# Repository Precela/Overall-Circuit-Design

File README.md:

# Overall-Circuit-Design
Schematic and PCB design for AR101

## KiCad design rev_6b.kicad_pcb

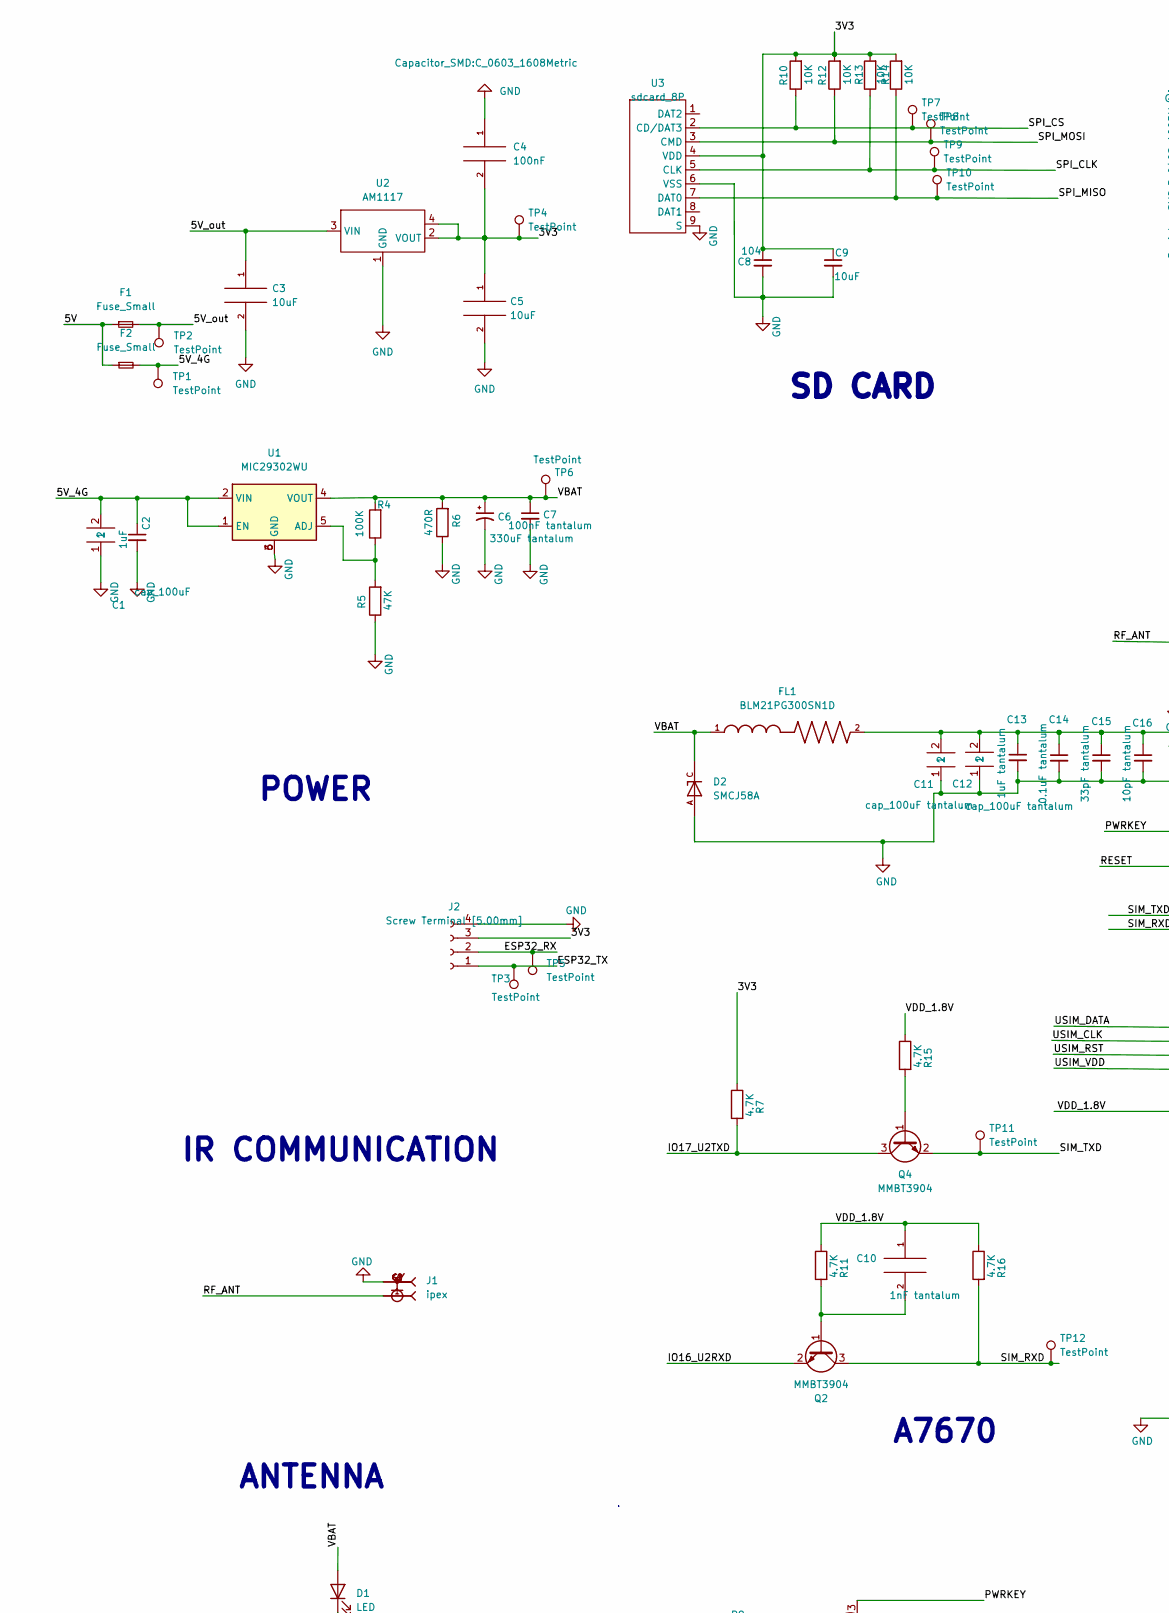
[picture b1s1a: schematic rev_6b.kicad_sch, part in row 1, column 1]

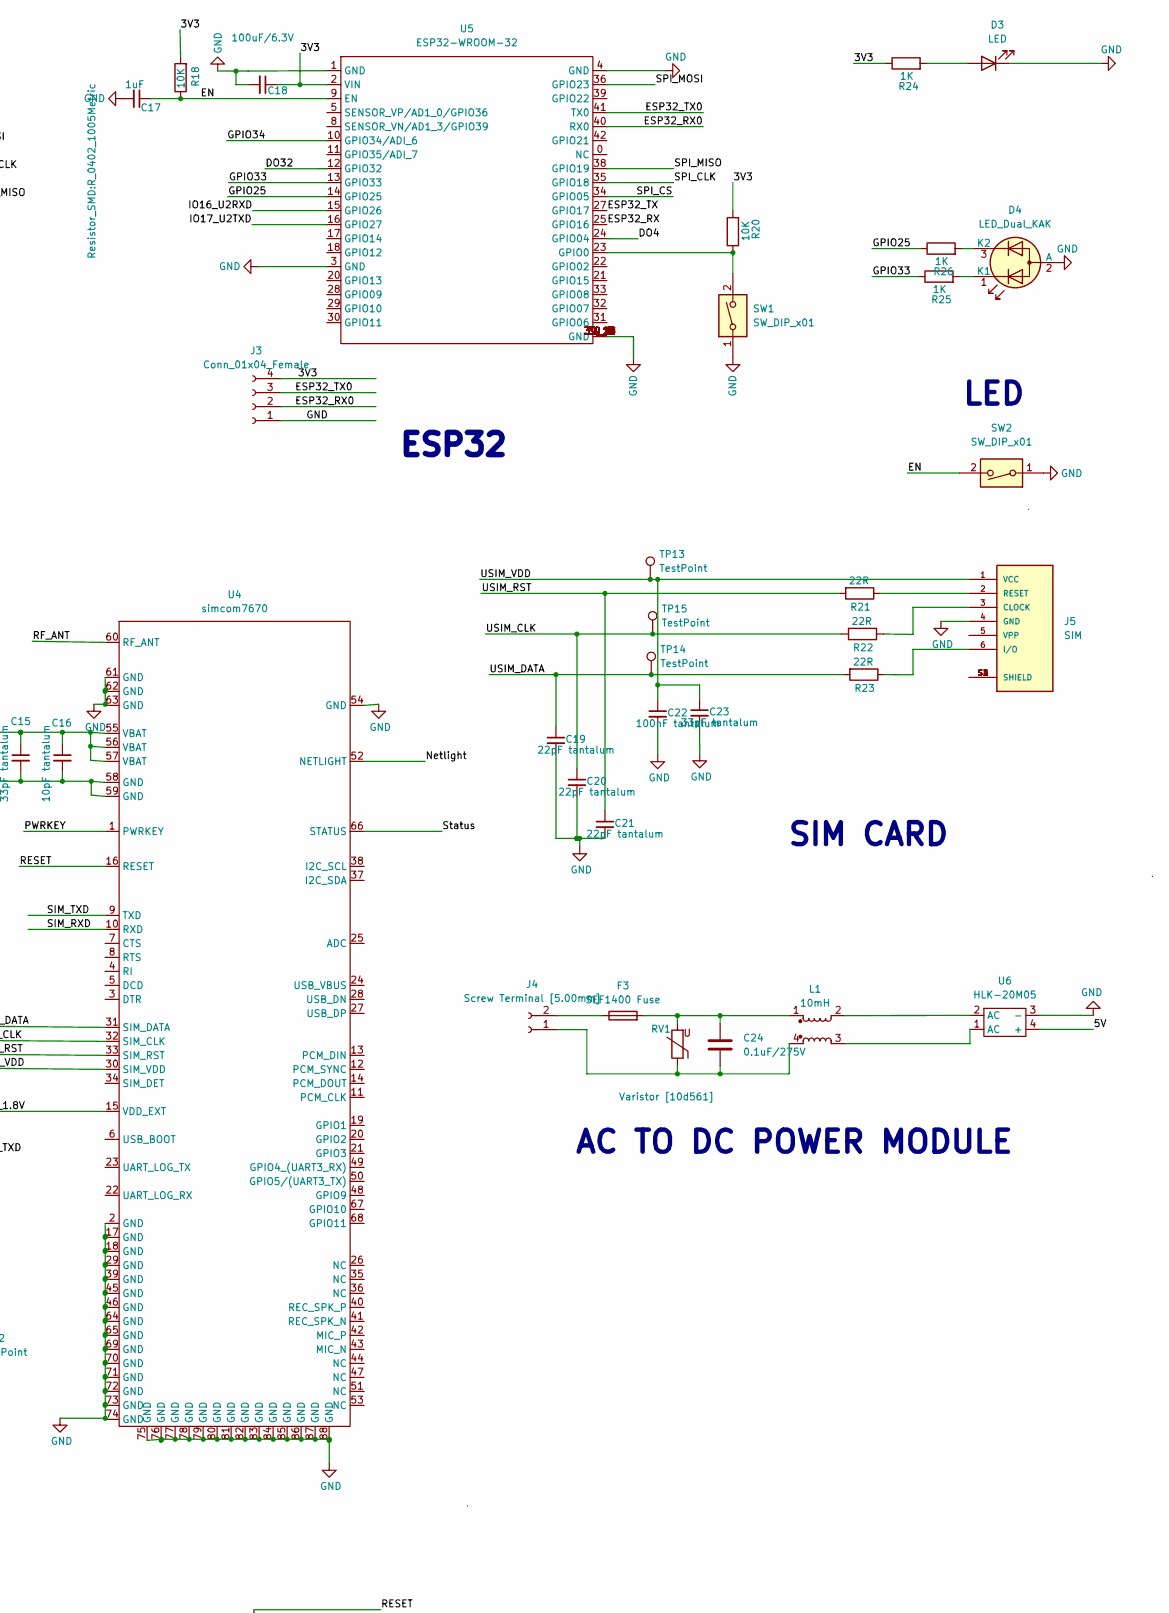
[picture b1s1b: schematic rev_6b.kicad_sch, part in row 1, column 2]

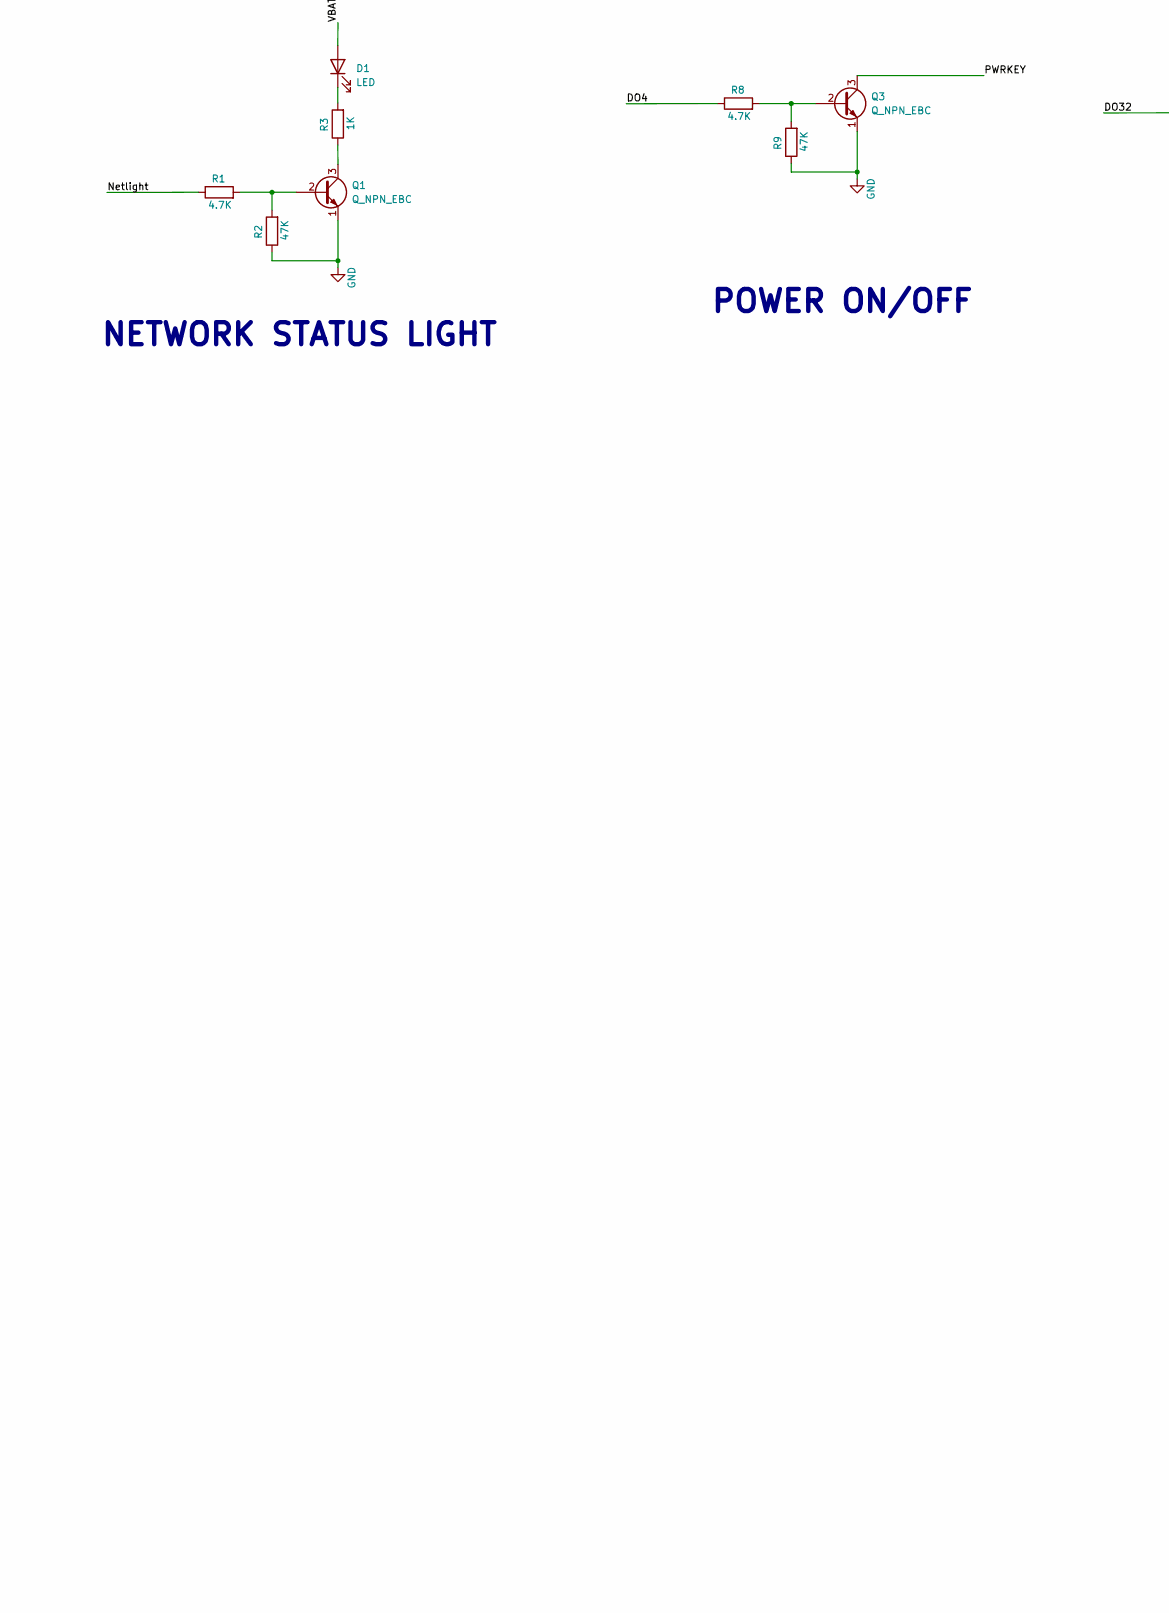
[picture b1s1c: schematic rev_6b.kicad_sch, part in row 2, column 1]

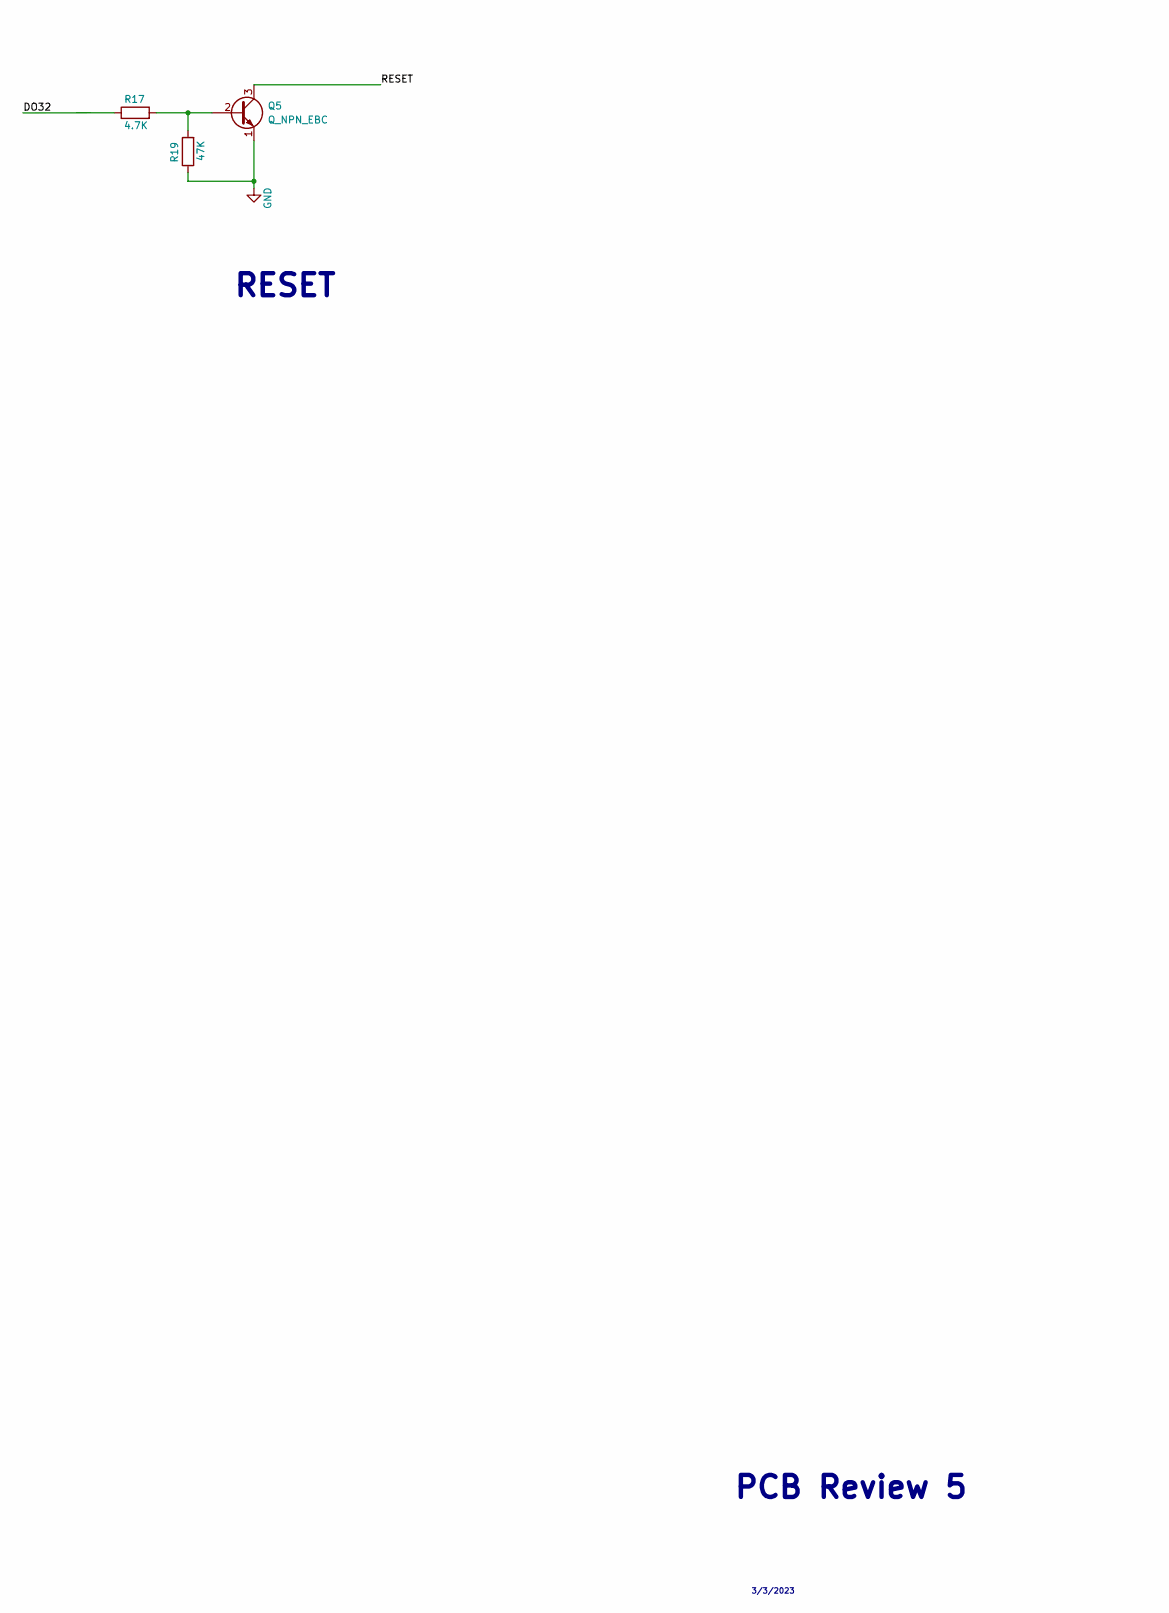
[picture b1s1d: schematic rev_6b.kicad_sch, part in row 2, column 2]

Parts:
C1: cap_100uF; C_0603_1608Metric
C2, C17: 1uF; C_0603_1608Metric
C3, C5, C9: 10uF; C_0603_1608Metric
C4: 100nF; C_0603_1608Metric
C6: 330uF tantalum; CAPMP7343X310N
C7, C22: 100nF tantalum; C_0603_1608Metric
C8: 104; C_0603_1608Metric
C10: 1nF tantalum; C_0603_1608Metric_Pad1.08x0.95mm_HandSolder
C11, C12: cap_100uF tantalum; C_0805_2012Metric
C13: 1uF tantalum; C_0603_1608Metric
C14: 0.1uF tantalum; C_1206_3216Metric
C15, C23: 33pF tantalum; C_0603_1608Metric
C16: 10pF tantalum; C_0603_1608Metric
C18: 100uF/6.3V; C_0603_1608Metric
C19, C20, C21: 22pF tantalum; C_0603_1608Metric
C24: 0.1uF/275V; C_Rect_L13.0mm_W6.0mm_P10.00mm_FKS3_FKP3_MKS4
D1, D3: LED; LED_D3.0mm
D2: SMCJ58A; DIOM7959X250N; PARTREV 5-2
D4: LED_Dual_KAK; LED_D3.0mm-3
F1, F2: Fuse_Small; Fuse_0603_1608Metric
F3: SEF1400 Fuse
FL1: BLM21PG300SN1D; BEADC2012X105N
J1: ipex; IPEX_20579-001E; PARTREV 11
J2: Screw Terminal [5.00mm]; PinHeader_1x04_P2.54mm_Vertical
J3: Conn_01x04_Female; PinHeader_1x04_P2.54mm_Vertical
J4: Screw Terminal [5.00mm]; TerminalBlock_bornier-2_P5.08mm
J5: SIM; sim_card; PARTREV F
L1: 10mH; inductor
Q1, Q3, Q5: Q_NPN_EBC; transistor_sot23
Q2, Q4: MMBT3904; SOT-23
R1, R7, R8, R11, R15, R16, R17: 4.7K; R_0402_1005Metric
R2, R5, R9, R19: 47K; R_0402_1005Metric
R3, R24, R25, R26: 1K; R_0402_1005Metric
R4: 100K; R_0402_1005Metric
R6: 470R; R_0402_1005Metric
R10, R12, R13, R14, R18, R20: 10K; R_0402_1005Metric
R21, R22, R23: 22R; R_0402_1005Metric
RV1: Varistor [10d561]; RV_Disc_D12mm_W3.9mm_P7.5mm
SW1, SW2: SW_DIP_x01; DIP_Sw
TP1, TP2, TP3, TP4, TP5, TP6, TP7, TP8, TP9, TP10, TP11, TP12, TP13, TP14, TP15: TestPoint; TestPoint_Pad_D1.0mm
U1: MIC29302WU; DPAK6P170_1524X459L254X81N
U2: AM1117; SOT229P700X180-4N
U3: sdcard_8P; sdcard_8p
U4: simcom7670; simcom-a7670e
U5: ESP32-WROOM-32; MODULE_ESP32-WROOM-32
U6: HLK-20M05; HILINK_4a

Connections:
/3V3: C4.2, C5.1, C8.1, C9.1, C18.1, J2.3, J3.4, R7.1, R10.2, R12.2, R13.2, R14.2, R18.2, R20.2, R24.1, TP4.1, U2.2 (VOUT), U2.4, U3.4 (VDD), U5.2 (VIN)
/5V: F1.1, F2.1, U6.4 (+)
/5V_4G: C1.2, C2.1, F2.2, TP1.1, U1.1 (EN), U1.2 (VIN)
/5V_out: C3.1, F1.2, TP2.1, U2.3 (VIN)
/DO4: R8.1, U5.24 (GPIO04)
/DO32: R17.1, U5.12 (GPIO32)
/EN: C17.1, R18.1, SW2.2, U5.9 (EN); also elsewhere on the board
/ESP32_RX: J2.2, TP5.1, U5.25 (GPIO16)
/ESP32_RX0: J3.2, U5.40 (RX0)
/ESP32_TX: J2.1, TP3.1, U5.27 (GPIO17)
/ESP32_TX0: J3.3, U5.41 (TX0)
/GPIO25: R26.1, U5.14 (GPIO25)
/GPIO33: R25.1, U5.13 (GPIO33)
/GPIO34: U5.10 (GPIO34/ADI_6)
/IO16_U2RXD: Q2.2 (E), U5.15 (GPIO26)
/IO17_U2TXD: Q4.3 (C), R7.2, U5.16 (GPIO27)
/Netlight: R1.1, U4.52 (NETLIGHT)
/PWRKEY: Q3.3 (C), U4.1 (PWRKEY)
/RESET: Q5.3 (C), U4.16 (RESET)
/RF_ANT: J1.1, U4.60 (RF_ANT)
/SIM_RXD: Q2.3 (C), R16.2, TP12.1, U4.10 (RXD)
/SIM_TXD: Q4.2 (E), TP11.1, U4.9 (TXD)
/SPI_CLK: R13.1, TP9.1, U3.5 (CLK), U5.35 (GPIO18)
/SPI_CS: R10.1, TP7.1, U3.2 (CD/DAT3), U5.34 (GPIO05)
/SPI_MISO: R14.1, TP10.1, U3.7 (DAT0), U5.38 (GPIO19)
/SPI_MOSI: R12.1, TP8.1, U3.3 (CMD), U5.36 (GPIO23)
/Status: U4.66 (STATUS)
/USIM_CLK: C20.1, R22.2, TP15.1, U4.32 (SIM_CLK)
/USIM_DATA: C19.1, R23.2, TP14.1, U4.31 (SIM_DATA)
/USIM_RST: C21.1, R21.2, U4.33 (SIM_RST)
/USIM_VDD: C22.1, C23.1, J5.1 (VCC), TP13.1, U4.30 (SIM_VDD)
/VBAT: C6.1, C7.1, D1.2 (A), D2.C, FL1.1, R4.2, R6.2, TP6.1, U1.4 (VOUT)
/VDD_1.8V: C10.1, R11.1, R15.1, R16.1, U4.15 (VDD_EXT)
GND: C1.1, C2.2, C3.2, C4.1, C5.2, C6.2, C7.2, C8.2, C9.2, C11.1, C12.1, C13.2, C14.2, C15.2, C16.2, C17.2, C18.2, C19.2, C20.2, C21.2, C22.2, C23.2, D2.A, D3.1 (K), D4.2 (A), J1.G1, J1.G2, J1.G3, J2.4, J3.1, J5.4 (GND), Q1.1 (E), Q3.1 (E), Q5.1 (E), R2.1, R5.1, R6.1, R9.1, R19.1, SW1.1, SW2.1, U1.3 (GND), U1.6 (GND), U2.1 (GND), U3.6 (VSS), U3.9 (S), U4.2 (GND), U4.17 (GND), U4.18 (GND), U4.29 (GND), U4.39 (GND), U4.45 (GND), U4.46 (GND), U4.54 (GND), U4.58 (GND), U4.59 (GND), U4.61 (GND), U4.62 (GND), U4.63 (GND), U4.64 (GND), U4.65 (GND), U4.69 (GND), U4.70 (GND), U4.71 (GND), U4.72 (GND), U4.73 (GND), U4.74 (GND), U4.75 (GND), U4.76 (GND), U4.77 (GND), U4.78 (GND), U4.79 (GND), U4.80 (GND), U4.81 (GND), U4.82 (GND), U4.83 (GND), U4.84 (GND), U4.85 (GND), U4.86 (GND), U4.87 (GND), U4.88 (GND), U5.1 (GND), U5.3 (GND), U5.4 (GND), U5.39_1 (GND), U5.39_2 (GND), U5.39_3 (GND), U5.39_4 (GND), U5.39_5 (GND), U5.39_6 (GND), U5.39_7 (GND), U5.39_8 (GND), U5.39_9 (GND), U5.39_10 (GND), U5.39_11 (GND), U5.39_12 (GND), U5.39_13 (GND), U5.39_14 (GND), U5.39_15 (GND), U5.39_16 (GND), U5.39_17 (GND), U5.39_18 (GND), U5.39_19 (GND), U5.39_20 (GND), U5.39_21 (GND), U6.3 (-); also elsewhere on the board
unnamed: C10.2, Q2.1 (B), R11.2
unnamed: C11.2, C12.2, C13.1, C14.1, C15.1, C16.1, FL1.2, U4.55 (VBAT), U4.56 (VBAT), U4.57 (VBAT)
unnamed: C24.1, F3.2, L1.1, RV1.2
unnamed: C24.2, J4.1, L1.4, RV1.1
unnamed: D1.1 (K), R3.2
unnamed: D3.2 (A), R24.2
unnamed: D4.1 (K1), R25.2
unnamed: D4.3 (K2), R26.2
unnamed: F3.1, J4.2
unnamed: J5.2 (RESET), R21.1
unnamed: J5.3 (CLOCK), R22.1
unnamed: J5.6 (I/O), R23.1
unnamed: L1.2, U6.2 (AC)
unnamed: L1.3, U6.1 (AC)
unnamed: Q1.2 (B), R1.2, R2.2
unnamed: Q1.3 (C), R3.1
unnamed: Q3.2 (B), R8.2, R9.2
unnamed: Q4.1 (B), R15.2
unnamed: Q5.2 (B), R17.2, R19.2
unnamed: R4.1, R5.2, U1.5 (ADJ)
unnamed: R20.1, SW1.2, U5.23 (GPIO0)

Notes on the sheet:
3/3/2023
POWER ON/OFF
A7670
POWER
NETWORK STATUS LIGHT
RESET
ESP32
PCB Review 5
ANTENNA
AC TO DC POWER MODULE
SD CARD
LED
IR COMMUNICATION
SIM CARD

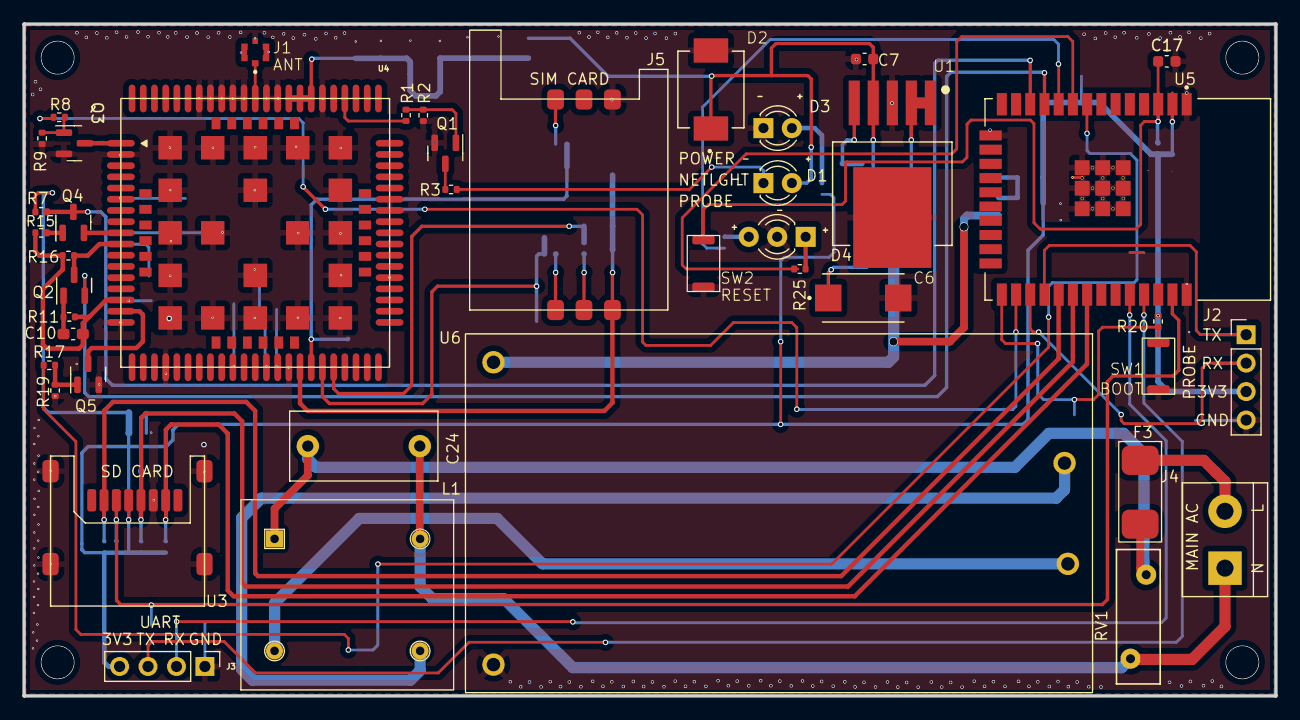
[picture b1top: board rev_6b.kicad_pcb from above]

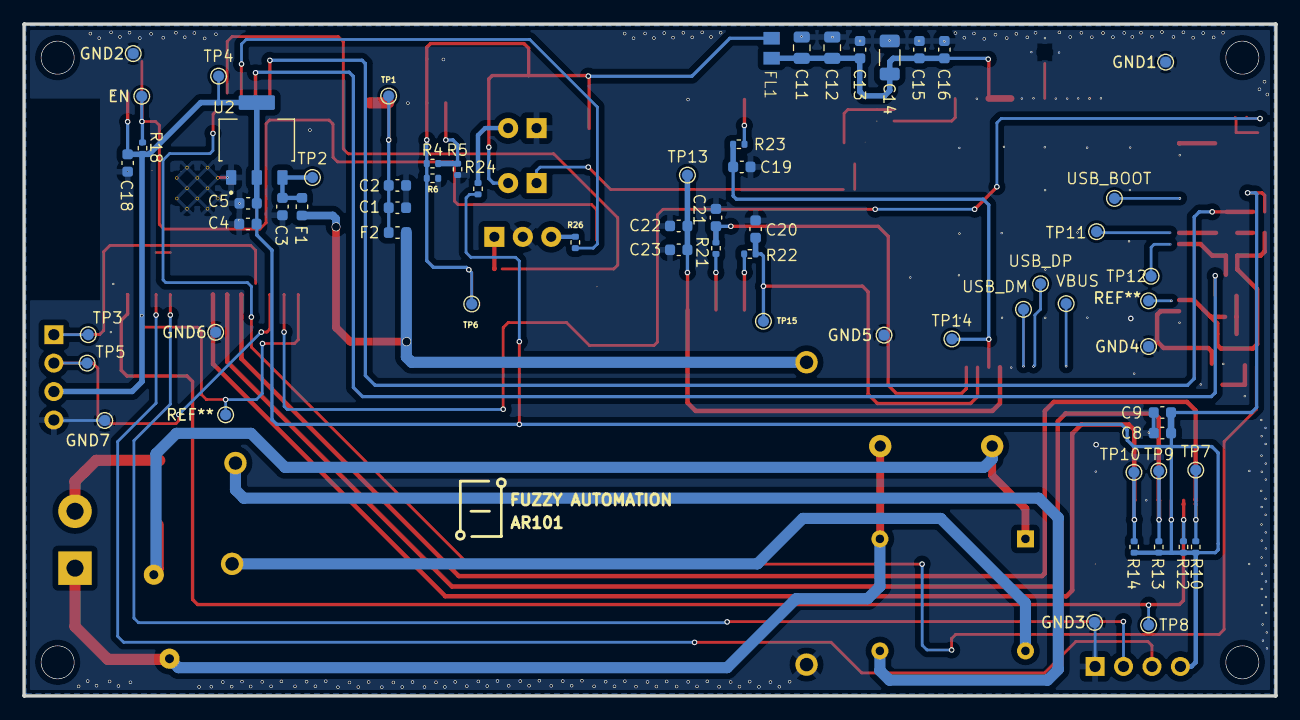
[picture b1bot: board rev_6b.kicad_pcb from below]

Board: 2 copper layers, 111.8 x 60.0 mm, 105 parts (63 on the bottom side), 53 nets.

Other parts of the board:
EN: TestPoint_Pad_D1.0mm
GND1, GND2, GND3, GND4, GND5, GND6, GND7: TestPoint_Pad_D1.0mm
USB_BOOT: TestPoint_Pad_D1.0mm
USB_DM: TestPoint_Pad_D1.0mm
USB_DP: TestPoint_Pad_D1.0mm
VBUS: TestPoint_Pad_D1.0mm

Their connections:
/EN: EN.1; also elsewhere on the board
GND: GND1.1, GND2.1, GND3.1, GND4.1, GND5.1, GND6.1, GND7.1; also elsewhere on the board
